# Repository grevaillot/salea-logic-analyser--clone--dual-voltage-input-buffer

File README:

Saleae Logic 8-bit 1v8 Input Buffer

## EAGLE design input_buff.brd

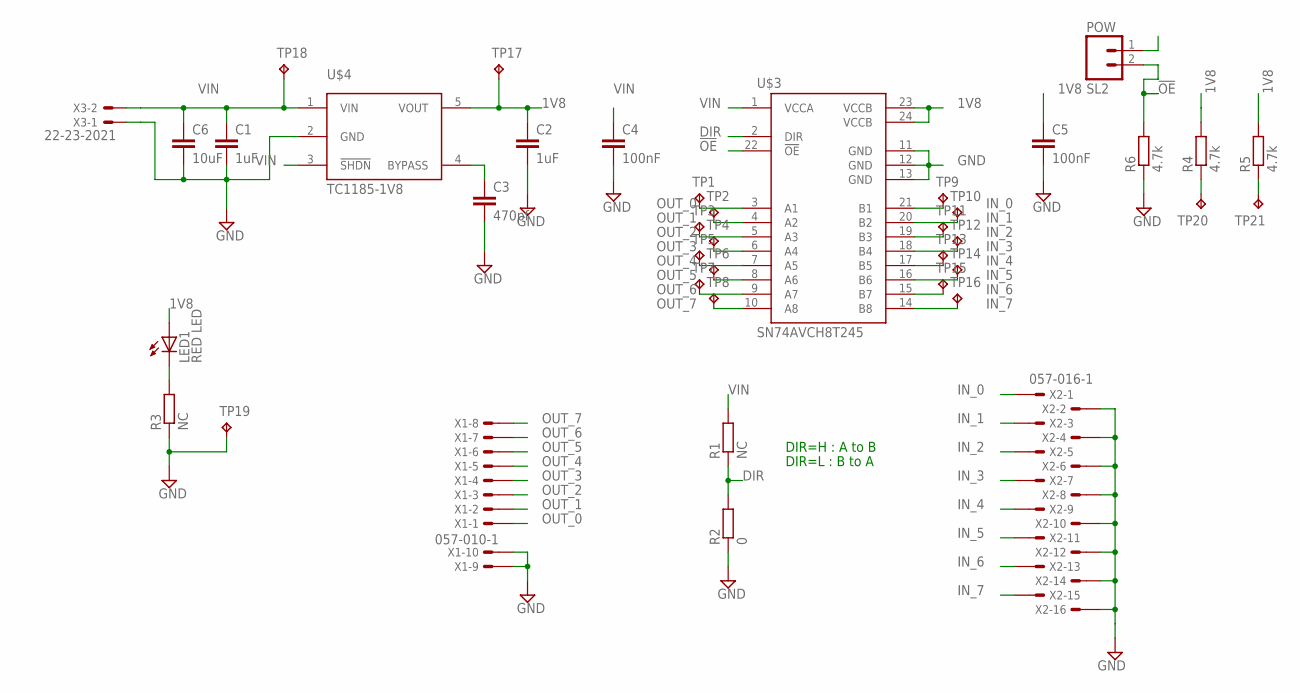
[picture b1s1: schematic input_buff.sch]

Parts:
C1, C2: 1uF; C0805
C3: 470pf; C0805
C4, C5: 100nF; C0805
C6: 10uF; C1210
LED1: RED LED; CHIPLED_0805
R1, R3: NC; M0805
R2: 0; M0805
R4, R5, R6: 4.7k; M0805
SL2: POW; 02P
TP1, TP2, TP3, TP4, TP5, TP6, TP7, TP8, TP9, TP10, TP11, TP12, TP13, TP14, TP15, TP16, TP17, TP18, TP19, TP20, TP21: TPTP10R; TP10R
U$3: SN74AVCH8T245; TSSOP24
U$4: TC1185-1V8; SOT23-5
X1: 057-010-1
X2: 057-016-1
X3: 22-23-2021

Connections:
1V8: C2.1, C5.1, LED1.A, R4.2, R5.2, TP17.TP, U$3.23 (VCCB), U$3.24 (VCCB), U$4.5 (VOUT)
!OE: R6.2, SL2.2, U$3.22 (!OE)
DIR: R1.1, R2.2, U$3.2 (DIR)
GND: C1.2, C2.2, C3.2, C4.2, C5.2, C6.2, R2.1, R3.1, R6.1, TP19.TP, U$3.11 (GND), U$3.12 (GND), U$3.13 (GND), U$4.2 (GND), X1.9, X1.10, X2.2, X2.4, X2.6, X2.8, X2.10, X2.12, X2.14, X2.16, X3.1
IN_0: TP9.TP, U$3.21 (B1), X2.1
IN_1: TP10.TP, U$3.20 (B2), X2.3
IN_2: TP11.TP, U$3.19 (B3), X2.5
IN_3: TP12.TP, U$3.18 (B4), X2.7
IN_4: TP13.TP, U$3.17 (B5), X2.9
IN_5: TP14.TP, U$3.16 (B6), X2.11
IN_6: TP15.TP, U$3.15 (B7), X2.13
IN_7: TP16.TP, U$3.14 (B8), X2.15
unnamed: R4.1, TP20.TP
unnamed: C3.1, U$4.4 (BYPASS)
unnamed: LED1.C, R3.2
unnamed: R5.1, TP21.TP
OUT_0: TP1.TP, U$3.3 (A1), X1.1
OUT_1: TP2.TP, U$3.4 (A2), X1.2
OUT_2: TP3.TP, U$3.5 (A3), X1.3
OUT_3: TP4.TP, U$3.6 (A4), X1.4
OUT_4: TP5.TP, U$3.7 (A5), X1.5
OUT_5: TP6.TP, U$3.8 (A6), X1.6
OUT_6: TP7.TP, U$3.9 (A7), X1.7
OUT_7: TP8.TP, U$3.10 (A8), X1.8
VIN: C1.1, C4.1, C6.1, R1.2, SL2.1, TP18.TP, U$3.1 (VCCA), U$4.1 (VIN), U$4.3 (!SHDN), X3.2

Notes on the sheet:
DIR=H : A to B
DIR=L : B to A

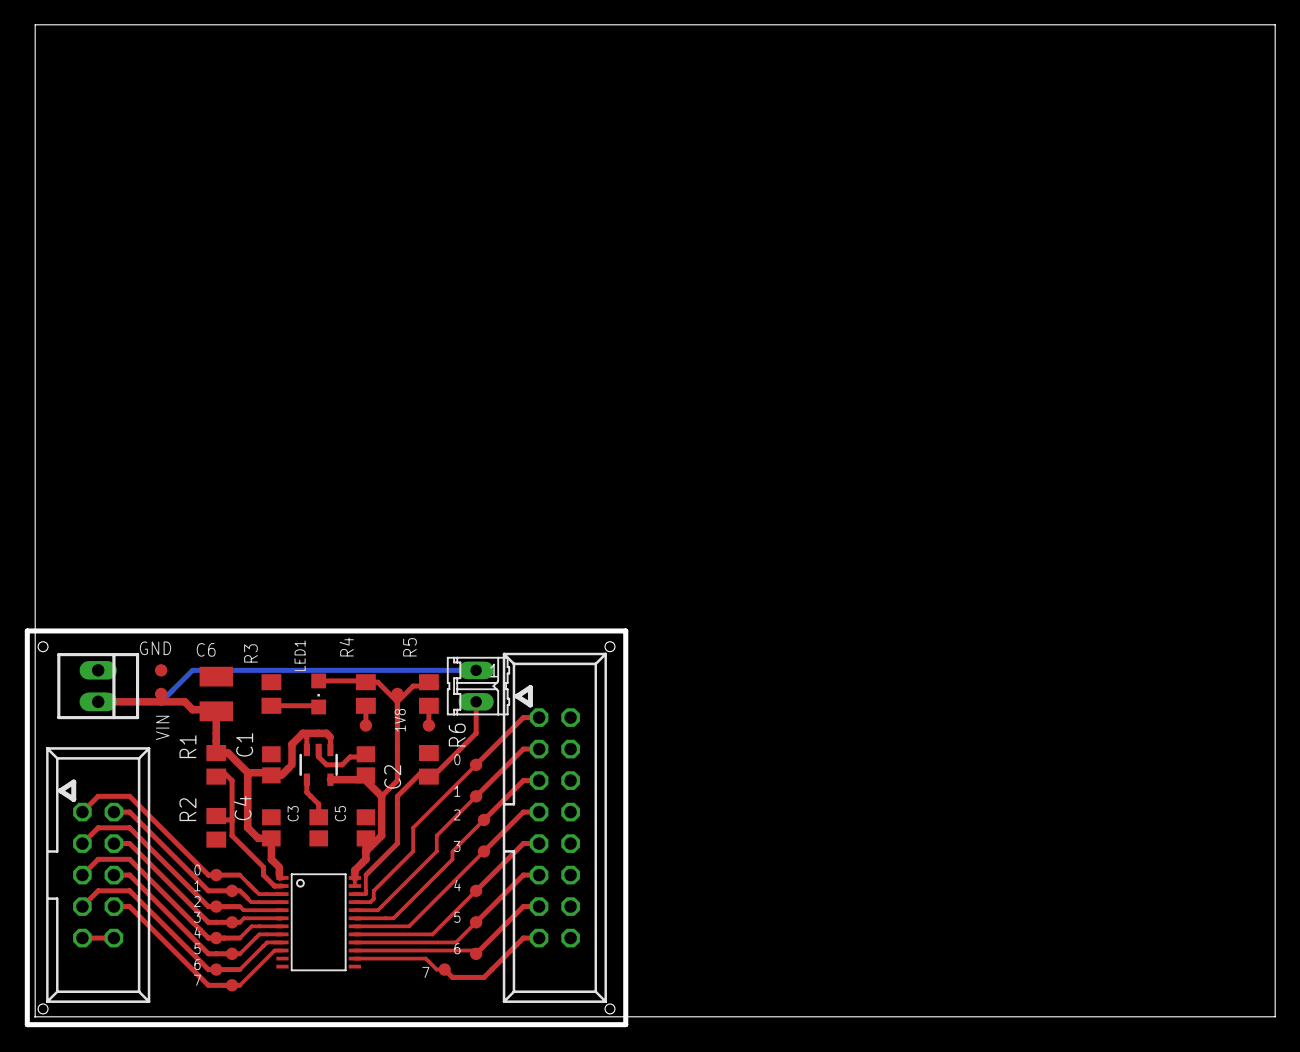
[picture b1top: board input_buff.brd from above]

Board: 2 copper layers, 100.4 x 80.4 mm, 40 parts (0 on the bottom side), 25 nets.

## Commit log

2011-12-30 readme
2011-12-30 .gitignore
2011-12-30 schematics ok, routing started
2011-12-30 remains drc pass.
2011-12-30 fusion pcb drc pass add two TP connected to 1V8 rail through a resistor, to be able to hack a pullup on an input signal "just in case".
2011-12-30 add gerbers
2011-12-31 fix drc for itead, update gerbers
2012-01-15 change led to cms, add addtionnal capa place
    add an addtionnal 1206 capa before ldo
    change led to 0805 smd
2012-03-04 final design + matching gerbers (production files)
